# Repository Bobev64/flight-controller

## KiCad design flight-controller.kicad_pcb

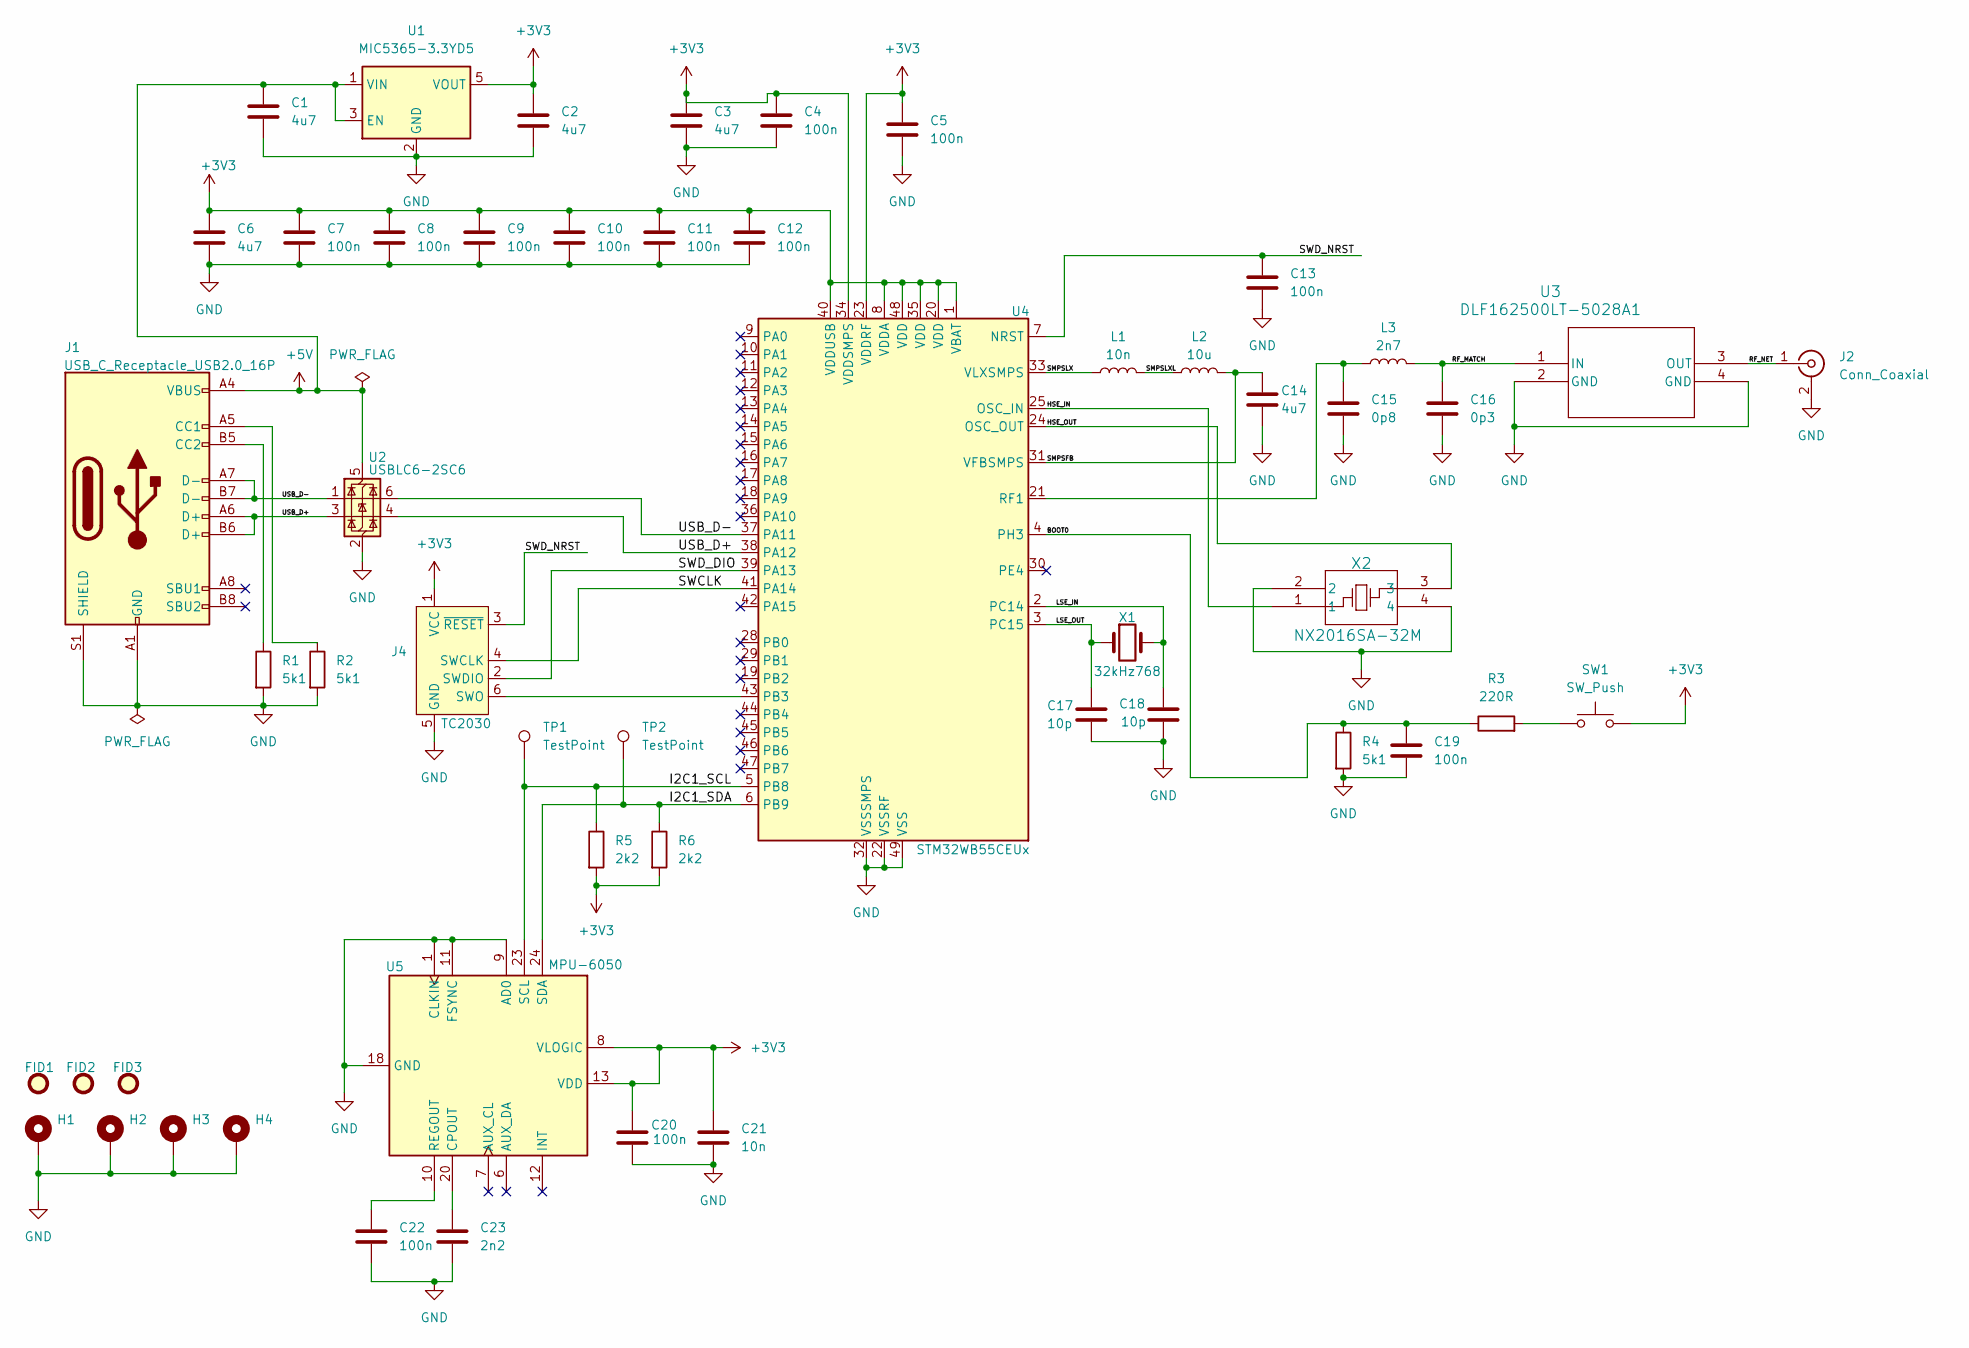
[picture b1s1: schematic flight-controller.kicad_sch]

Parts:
C1, C2, C3, C6, C14: 4u7; C_0603_1608Metric; Manufacturer Part # 0603ZD475MAT2A
C4, C5, C7, C8, C9, C10, C11, C12, C13, C19, C20, C22: 100n; C_0402_1005Metric; Manufacturer Part # KGM05AR51A104KH
C15: 0p8; C_0402_1005Metric; Manufacturer Part # 04025U0R8BAT2A
C16: 0p3; C_0402_1005Metric; Manufacturer Part # GRM1555C1HR30BA01J
C17, C18: 10p; C_0402_1005Metric; Manufacturer Part # GRM1555C1H100JA01D
C21: 10n; C_0402_1005Metric; Manufacturer Part # GRM155R71C103KA01D
C23: 2n2; C_0402_1005Metric; Manufacturer Part # GRM155R61C222KA01D
FID1, FID2, FID3: Fiducial; Fiducial_1mm_Mask2mm
H1, H2, H3, H4: MountingHole_Pad; MountingHole_2.2mm_M2_Pad
J1: USB_C_Receptacle_USB2.0_16P; USB_C_Receptacle_GCT_USB4105-xx-A_16P_TopMnt_Horizontal; Manufacturer Part # USB4105-GF-A
J2: Conn_Coaxial; U.FL_Hirose_U.FL-R-SMT-1_Vertical; Manufacturer Part # U.FL-R-SMT-1(01)
J4: TC2030; Tag-Connect_TC2030-IDC-NL_2x03_P1.27mm_Vertical
L1: 10n; L_0402_1005Metric; Manufacturer Part # LQG15WZ10NJ02D
L2: 10u; L_0805_2012Metric; Manufacturer Part # LQM21FN100m70L
L3: 2n7; L_0402_1005Metric; Manufacturer Part # LQG15HS2N7S02
R1, R2, R4: 5k1; R_0402_1005Metric; Manufacturer Part # ERJ-2GEJ512X
R3: 220R; R_0402_1005Metric; Manufacturer Part # RC0402JR-07220RL
R5, R6: 2k2; R_0402_1005Metric; Manufacturer Part # ERJ-2RKF2201X
SW1: SW_Push; SW_SPST_CK_RS282G05A3; Manufacturer Part # RS-282G05A3-SM RT
TP1, TP2: TestPoint; TestPoint_Pad_D1.0mm
U1: MIC5365-3.3YD5; SOT-23-5; Manufacturer Part # MIC5365-3.3YD5-TR
U2: USBLC6-2SC6; SOT-23-6; Manufacturer Part # USBLC6-2SC6
U3: DLF162500LT-5028A1; DLF-4_1P6X0P8; Manufacturer Part # DLF162500LT-5028A1
U4: STM32WB55CEUx; QFN-48-1EP_7x7mm_P0.5mm_EP5.6x5.6mm; Manufacturer Part # STM32WB55CEU6
U5: MPU-6050; InvenSense_QFN-24_4x4mm_P0.5mm; Manufacturer Part # MPU-6050
X1: 32kHz768; XTAL_NX2012SA_NDK; Manufacturer Part # STDMUB1-32.768K
X2: NX2016SA-32M; NX2016SA_NDK; Manufacturer Part # CS06465-32M

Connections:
+3V3: C2.1, C3.1, C4.1, C5.1, C6.1, C7.1, C8.1, C9.1, C10.1, C11.1, C12.1, C20.1, C21.1, J4.1 (VCC), R5.2, R6.2, SW1.2, U1.5 (VOUT), U4.1 (VBAT), U4.8 (VDDA), U4.20 (VDD), U4.23 (VDDRF), U4.34 (VDDSMPS), U4.35 (VDD), U4.40 (VDDUSB), U4.48 (VDD), U5.8 (VLOGIC), U5.13 (VDD)
+5V: C1.1, J1.A4 (VBUS), J1.A9 (VBUS), J1.B4 (VBUS), J1.B9 (VBUS), U1.1 (VIN), U1.3 (EN), U2.5 (VBUS)
/BOOT0: C19.1, R3.1, R4.1, U4.4 (PH3)
/HSE_IN: U4.25 (OSC_IN), X2.1
/HSE_OUT: U4.24 (OSC_OUT), X2.3
/I2C1_SCL: R5.1, TP1.1, U4.5 (PB8), U5.23 (SCL)
/I2C1_SDA: R6.1, TP2.1, U4.6 (PB9), U5.24 (SDA)
/LSE_IN: C18.1, U4.2 (PC14), X1.2
/LSE_OUT: C17.1, U4.3 (PC15), X1.1
/RF_MATCH: C16.1, L3.2, U3.1 (IN)
/RF_NET: J2.1 (In), U3.3 (OUT)
/SMPSFB: C14.1, L2.2, U4.31 (VFBSMPS)
/SMPSLX: L1.1, U4.33 (VLXSMPS)
/SMPSLXL: L1.2, L2.1
/SWCLK: J4.4 (SWCLK), U4.41 (PA14)
/SWD_DIO: J4.2 (SWDIO), U4.39 (PA13)
/SWD_NRST: C13.1, J4.3 (~RESET), U4.7 (NRST)
/USB_D+: J1.A6 (D+), J1.B6 (D+), U2.3 (I/O2), U2.4 (I/O2), U4.38 (PA12)
/USB_D-: J1.A7 (D-), J1.B7 (D-), U2.1 (I/O1), U2.6 (I/O1), U4.37 (PA11)
GND: C1.2, C2.2, C3.2, C4.2, C5.2, C6.2, C7.2, C8.2, C9.2, C10.2, C11.2, C12.2, C13.2, C14.2, C15.2, C16.2, C17.2, C18.2, C19.2, C20.2, C21.2, C22.2, C23.2, H1.1, H2.1, H3.1, H4.1, J1.A1 (GND), J1.A12 (GND), J1.B1 (GND), J1.B12 (GND), J1.S1 (SHIELD), J2.2 (Ext), J4.5 (GND), R1.2, R2.2, R4.2, U1.2 (GND), U2.2 (GND), U3.2 (GND), U3.4 (GND), U4.22 (VSSRF), U4.32 (VSSSMPS), U4.49 (VSS), U5.1 (CLKIN), U5.9 (AD0), U5.11 (FSYNC), U5.18 (GND), X2.2, X2.4
unnamed: J1.A5 (CC1), R2.1
unnamed: J1.B5 (CC2), R1.1
unnamed: J4.6 (SWO), U4.43 (PB3)
unnamed: R3.2, SW1.1
unnamed: C15.1, L3.1, U4.21 (RF1)
unnamed: C23.1, U5.20 (CPOUT)
unnamed: C22.1, U5.10 (REGOUT)

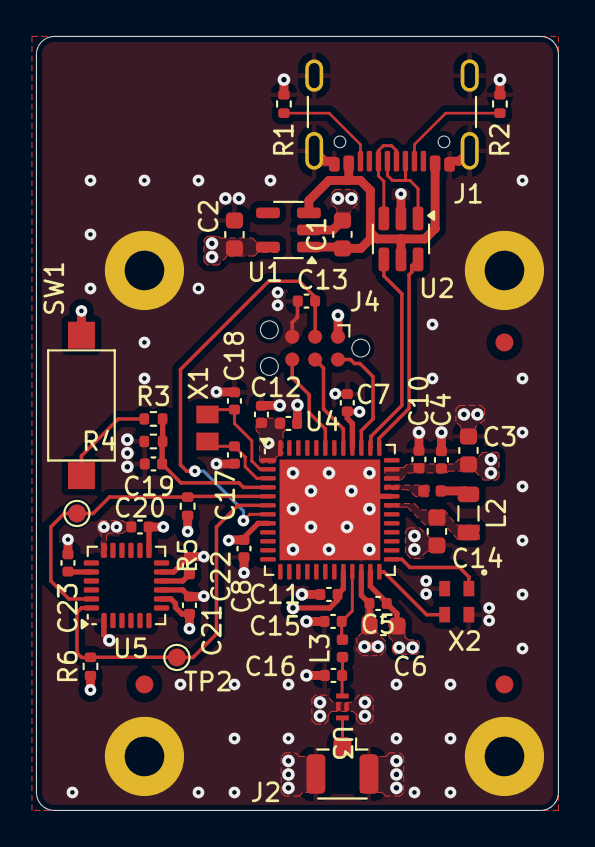
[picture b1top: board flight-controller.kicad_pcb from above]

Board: 4 copper layers, 29.0 x 43.0 mm, 52 parts (0 on the bottom side), 27 nets.

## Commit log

2024-06-17 init
2024-06-18 added gitignore, schematic updated
2024-06-18 added outline of imu, wip
2024-06-24 added footprints, started BOM
2024-06-25 added 3d models, start pcb layout
2024-06-26 initial layout of PCB continued
2024-07-01 finished layout
2024-07-02 begin routing, i2c layout refinement wip
2024-07-03 Routing continued. I2C mostly fixed up
2024-07-05 routing mostly complete
2024-07-08 BOM updates, minor routing improvements
2024-07-09 BOM done, footprints & layout updated.
    Layout for both crystal oscillators revised.
2024-07-14 almost no DRC errors
2024-07-23 added test points
